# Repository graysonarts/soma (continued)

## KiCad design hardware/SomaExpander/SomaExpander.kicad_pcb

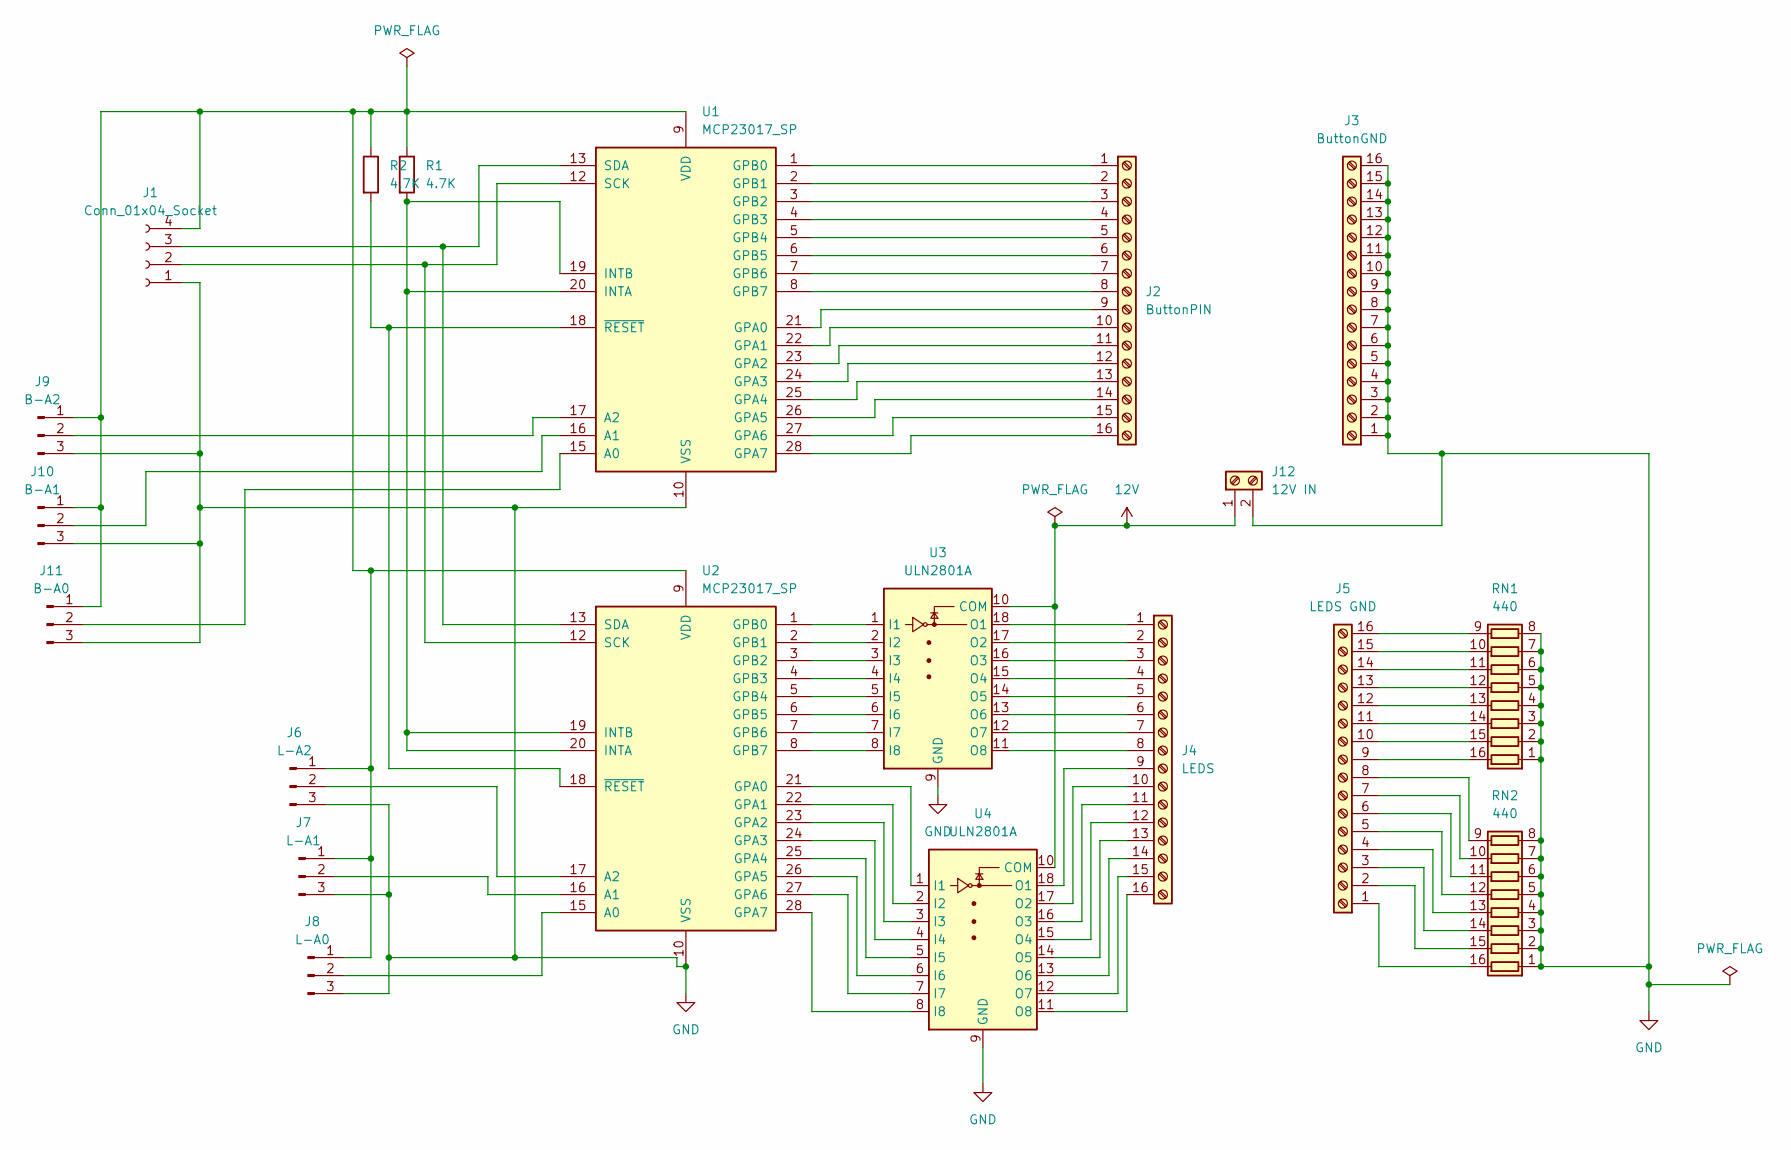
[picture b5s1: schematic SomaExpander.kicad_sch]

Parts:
J1: Conn_01x04_Socket; JST_EH_S4B-EH_1x04_P2.50mm_Horizontal
J2: ButtonPIN; Altech_AK100_1x16_P5.00mm
J3: ButtonGND; Altech_AK100_1x16_P5.00mm
J4: LEDS; Altech_AK100_1x16_P5.00mm
J5: LEDS GND; Altech_AK100_1x16_P5.00mm
J6: L-A2; FanPinHeader_1x03_P2.54mm_Vertical
J7: L-A1; FanPinHeader_1x03_P2.54mm_Vertical
J8: L-A0; FanPinHeader_1x03_P2.54mm_Vertical
J9: B-A2; FanPinHeader_1x03_P2.54mm_Vertical
J10: B-A1; FanPinHeader_1x03_P2.54mm_Vertical
J11: B-A0; FanPinHeader_1x03_P2.54mm_Vertical
J12: 12V IN; TerminalBlock_4Ucon_1x02_P3.50mm_Vertical
R1, R2: 4.7K; R_0201_0603Metric
RN1, RN2: 440; SOIC-16W_5.3x10.2mm_P1.27mm
U1, U2: MCP23017_SP; DIP-28_W7.62mm
U3, U4: ULN2801A; SOIC-18W_7.5x11.6mm_P1.27mm

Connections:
12V: J12.1, U3.10 (COM), U4.10 (COM)
GND: J1.1, J3.1, J3.2, J3.3, J3.4, J3.5, J3.6, J3.7, J3.8, J3.9, J3.10, J3.11, J3.12, J3.13, J3.14, J3.15, J3.16, J6.3, J7.3, J8.3, J9.3, J10.3, J11.3, J12.2, RN1.1 (R1.1), RN1.2 (R2.1), RN1.3 (R3.1), RN1.4 (R4.1), RN1.5 (R5.1), RN1.6 (R6.1), RN1.7 (R7.1), RN1.8 (R8.1), RN2.1 (R1.1), RN2.2 (R2.1), RN2.3 (R3.1), RN2.4 (R4.1), RN2.5 (R5.1), RN2.6 (R6.1), RN2.7 (R7.1), RN2.8 (R8.1), U1.10 (VSS), U2.10 (VSS), U3.9 (GND), U4.9 (GND)
unnamed: J1.2, U1.12 (SCK), U2.12 (SCK)
unnamed: J1.3, U1.13 (SDA), U2.13 (SDA)
unnamed: J1.4, J6.1, J7.1, J8.1, J9.1, J10.1, J11.1, R1.1, R2.1, U1.9 (VDD), U2.9 (VDD)
unnamed: J2.1, U1.1 (GPB0)
unnamed: J2.2, U1.2 (GPB1)
unnamed: J2.3, U1.3 (GPB2)
unnamed: J2.4, U1.4 (GPB3)
unnamed: J2.5, U1.5 (GPB4)
unnamed: J2.6, U1.6 (GPB5)
unnamed: J2.7, U1.7 (GPB6)
unnamed: J2.8, U1.8 (GPB7)
unnamed: J2.9, U1.21 (GPA0)
unnamed: J2.10, U1.22 (GPA1)
unnamed: J2.11, U1.23 (GPA2)
unnamed: J2.12, U1.24 (GPA3)
unnamed: J2.13, U1.25 (GPA4)
unnamed: J2.14, U1.26 (GPA5)
unnamed: J2.15, U1.27 (GPA6)
unnamed: J2.16, U1.28 (GPA7)
unnamed: J4.1, U3.18 (O1)
unnamed: J4.2, U3.17 (O2)
unnamed: J4.3, U3.16 (O3)
unnamed: J4.4, U3.15 (O4)
unnamed: J4.5, U3.14 (O5)
unnamed: J4.6, U3.13 (O6)
unnamed: J4.7, U3.12 (O7)
unnamed: J4.8, U3.11 (O8)
unnamed: J4.9, U4.18 (O1)
unnamed: J4.10, U4.17 (O2)
unnamed: J4.11, U4.16 (O3)
unnamed: J4.12, U4.15 (O4)
unnamed: J4.13, U4.14 (O5)
unnamed: J4.14, U4.13 (O6)
unnamed: J4.15, U4.12 (O7)
unnamed: J4.16, U4.11 (O8)
unnamed: J5.1, RN2.16 (R1.2)
unnamed: J5.2, RN2.15 (R2.2)
unnamed: J5.3, RN2.14 (R3.2)
unnamed: J5.4, RN2.13 (R4.2)
unnamed: J5.5, RN2.12 (R5.2)
unnamed: J5.6, RN2.11 (R6.2)
unnamed: J5.7, RN2.10 (R7.2)
unnamed: J5.8, RN2.9 (R8.2)
unnamed: J5.9, RN1.16 (R1.2)
unnamed: J5.10, RN1.15 (R2.2)
unnamed: J5.11, RN1.14 (R3.2)
unnamed: J5.12, RN1.13 (R4.2)
unnamed: J5.13, RN1.12 (R5.2)
unnamed: J5.14, RN1.11 (R6.2)
unnamed: J5.15, RN1.10 (R7.2)
unnamed: J5.16, RN1.9 (R8.2)
unnamed: J6.2, U2.17 (A2)
unnamed: J7.2, U2.16 (A1)
unnamed: J8.2, U2.15 (A0)
unnamed: J9.2, U1.17 (A2)
unnamed: J10.2, U1.16 (A1)
unnamed: J11.2, U1.15 (A0)
unnamed: R1.2, U1.19 (INTB), U1.20 (INTA), U2.19 (INTB), U2.20 (INTA)
unnamed: R2.2, U1.18 (~RESET), U2.18 (~RESET)
unnamed: U2.21 (GPA0), U4.1 (I1)
unnamed: U2.22 (GPA1), U4.2 (I2)
unnamed: U2.23 (GPA2), U4.3 (I3)
unnamed: U2.24 (GPA3), U4.4 (I4)
unnamed: U2.25 (GPA4), U4.5 (I5)
unnamed: U2.26 (GPA5), U4.6 (I6)
unnamed: U2.27 (GPA6), U4.7 (I7)
unnamed: U2.28 (GPA7), U4.8 (I8)
unnamed: U2.1 (GPB0), U3.1 (I1)
unnamed: U2.2 (GPB1), U3.2 (I2)
unnamed: U2.3 (GPB2), U3.3 (I3)
unnamed: U2.4 (GPB3), U3.4 (I4)
unnamed: U2.5 (GPB4), U3.5 (I5)
unnamed: U2.6 (GPB5), U3.6 (I6)
unnamed: U2.7 (GPB6), U3.7 (I7)
unnamed: U2.8 (GPB7), U3.8 (I8)

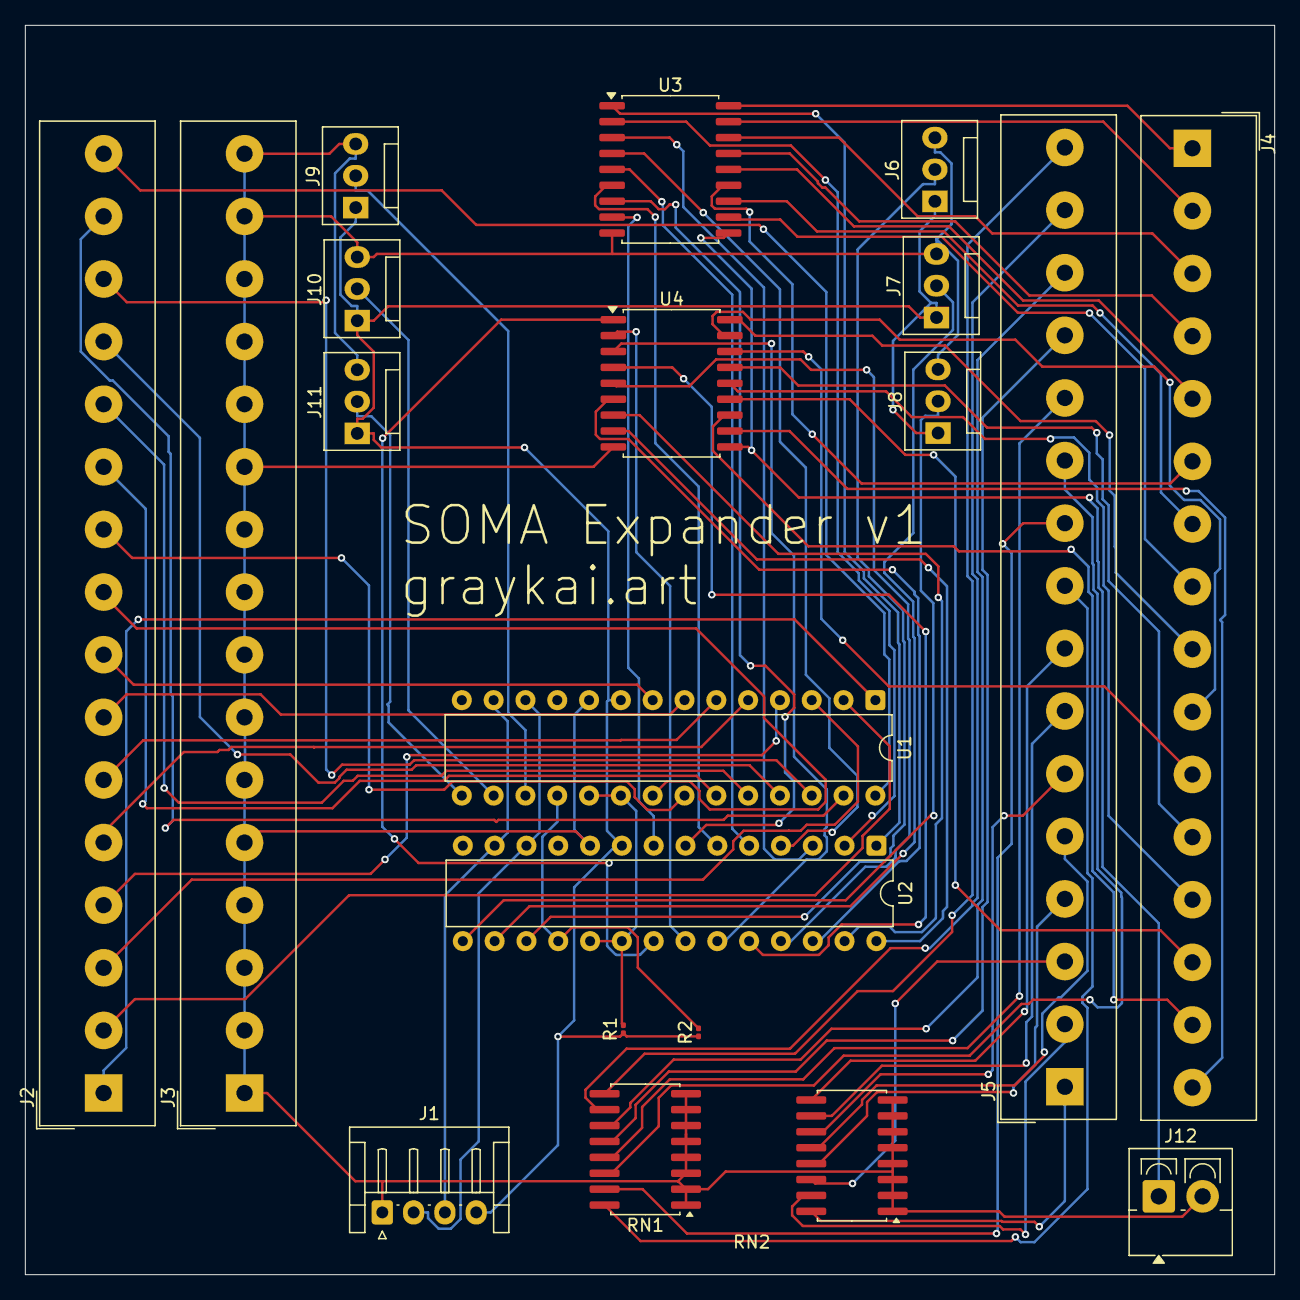
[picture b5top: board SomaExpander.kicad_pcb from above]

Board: 2 copper layers, 99.8 x 99.8 mm, 20 parts (0 on the bottom side), 77 nets.

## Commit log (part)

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2025-05-23 checkpoint
2025-05-23 initial blinky, not working, maybe?
2025-06-06 checkpoint for 12 and 12
2025-06-06 adding Pico2W pinouts
2025-06-06 Adding data sheet for the multiplexer
2025-06-06 Untested, but audio routing should work too
2025-06-26 Current Design. We need to split it into two boards I think.
2025-06-27 Checkpoint on hardware design
